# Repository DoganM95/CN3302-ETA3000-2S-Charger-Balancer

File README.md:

# Intro

A dual cell charger (3-6V 4A in, 8.4V ~3A out) combined with active balancing (1.3A).   
- The charging part makes sure to load the battery pack to 8.4v
- The balancing part makes sure to keep both batteries at the same voltage always, by charging the lower one using the higher one (active balancing)

Having these combined will in theory give the perfect 2S bms, so that batteries won't die, charge fast and don't waste energy.  

Any buyable bms i have tested so far fails to keep both batteries at the same voltage, so that one is e.g. 4.6v and the other 3.8v, resulting in 8.4v total but leading to damage/death of the overcharged cell, hence this proect to solve the issue and have a reliable, hackable solution.  

Still in concept phase, highly experimental and untested. Even the pcb traces are not wide enough to support the supplied current and would probably delaminate or catch fire.  

Releases starting with v1 or higher can be used and are tested.

# PCB

<table>
  <tr>
    <td>
      
    </td>
    <td>
      
    </td>
  </tr>
</table>

## BOM

Most parts a salvaged from commercially available modules, which are dirt-cheap on aliexpress:
- [Charging module (2S, 4A](https://a.aliexpress.com/_EuYAQFK)
- [Balancing module (2S, 1.3A, active)](https://s.click.aliexpress.com/e/_EuIdQJ6)

So all parts of those modules can be desoldered using a hot-plate and solder3d on this project's pcb.

<table>
  <thead>
    <tr>
      <th>Component Symbol</th>
      <th>Size</th>
      <th>Value</th>
      <th>Side Notes</th>
    </tr>
  </thead>
  <tbody>
    <tr><td>C1</td><td>0603</td><td>10nF</td><td></td></tr>
    <tr><td>C2</td><td>1206</td><td>22uF</td><td></td></tr>
    <tr><td>C3</td><td>0603</td><td>10nF</td><td></td></tr>
    <tr><td>C4</td><td>0603</td><td>10nF</td><td></td></tr>
    <tr><td>C5</td><td>0603</td><td>10nF</td><td></td></tr>
    <tr><td>C6</td><td>1206</td><td>22uF</td><td></td></tr>
    <tr><td>C7</td><td>1206</td><td>22uF</td><td></td></tr>
    <tr><td>C8</td><td>1206</td><td>22uF</td><td></td></tr>
    <tr><td>C9</td><td>1206</td><td>22uF</td><td></td></tr>
    <tr><td>C10</td><td>0603</td><td>10nF</td><td></td></tr>
    <tr><td>C11</td><td>1206</td><td>22uF</td><td></td></tr>
    <tr><td>C12</td><td>1206</td><td>22uF</td><td></td></tr>
    <tr><td>C13</td><td>1206</td><td>22uF</td><td></td></tr>
    <tr><td>C14</td><td>1206</td><td>22uF</td><td></td></tr>
    <tr><td>D1</td><td>sma</td><td>SS54 (Schottky)</td><td></td></tr>
    <tr><td>L1</td><td>0630 (6.6x6.6x3mm)</td><td>2.2 uH</td><td></td></tr>
    <tr><td>L2 / L3</td><td>any</td><td>2.2 uH</td><td>any that fits there by size</td></tr>
    <tr><td>LED1</td><td>0603</td><td>led</td><td>any color, check R3</td></tr>
    <tr><td>Q1</td><td>TO-252-2</td><td>KND3203b</td><td></td></tr>
    <tr><td>R1</td><td>0603</td><td>5.1 kOhm</td><td></td></tr>
    <tr><td>R2</td><td>0603</td><td>5.1 kOhm</td><td></td></tr>
    <tr><td>R3</td><td>0603</td><td>var Ohm</td><td>choose one that fits your LED1</td></tr>
    <tr><td>R4</td><td>0603</td><td>25 kOhm</td><td></td></tr>
    <tr><td>R5</td><td>2512</td><td>0.015 Ohm</td><td></td></tr>
    <tr><td>R6</td><td>0603</td><td>10 kOhm</td><td></td></tr>
    <tr><td>R7</td><td>0603</td><td>10 kOhm</td><td></td></tr>
    <tr><td>U1</td><td>sot23-6</td><td>ETA3000</td><td></td></tr>
    <tr><td>U2</td><td>smt</td><td>PC817X</td><td></td></tr>
    <tr><td>U3</td><td>sop8</td><td>CN3302</td><td></td></tr>
    <tr><td>U4</td><td>sot23-5</td><td>MIC5219 3.3v</td><td></td></tr>
  </tbody>
</table>

## Schematic

### By Datasheets

Follows the recommendations and schematics of the datasheets

### By reverse engineered chinese modules

Follows the reverse engineered chinese pcb modules, so they are merged into this pcb to minimize the need of additional components (just move parts over).

Todo

## Key Takeaways

- The status group of the `ETA3000` consisting of a red led and a 1k resistor use `BatC` as one pole and `SW` as the other. Thus it does not have a real `GND` but current flows with `BatC` acting as Vcc and `SW` acting as `GND` for the led
- The said red status led connections could also be exploited to power an optocoupler, so the `GND` stays independent for this part of the circuit and status becomes measurable using e.g. an arduino
- Connecting `BIAS` or `SW` of the `ETA3000` to the `GND`, which is the negative side of the 2 batteries connected in series, kills the IC and from there it gets very hot while being powered
- None of the 2 ic's (CN3302 && ETA3000) have a symbol in snapeda, so generic packages are used and pins renamed to match this ic

## Resources

### Charger IC: CN3302 (sop-8)

- [Datasheet (EN) of CN3302](https://github.com/DoganM95/2S-Charge-Balance-Pcb/files/13642784/CN3302.zh-CN.en.pdf)
- [Datasheet (CN) of CN3302](https://jlcpcb.com/partdetail/ShangHai_ConsonanceElec-CN3302/C559039)

### Active balancer IC: ETA3000 (sot23-6)
- [Writeup on ETA3000](https://www.beyondlogic.org/review-li-ion-lipo-lifepo4-lithium-battery-active-equalizer-balancer-energy-transfer-board/)
- [Datasheet of ETA3000](https://github.com/DoganM95/2S-Charge-Balance-Pcb/files/13648156/ETA3000-ETA.pdf)

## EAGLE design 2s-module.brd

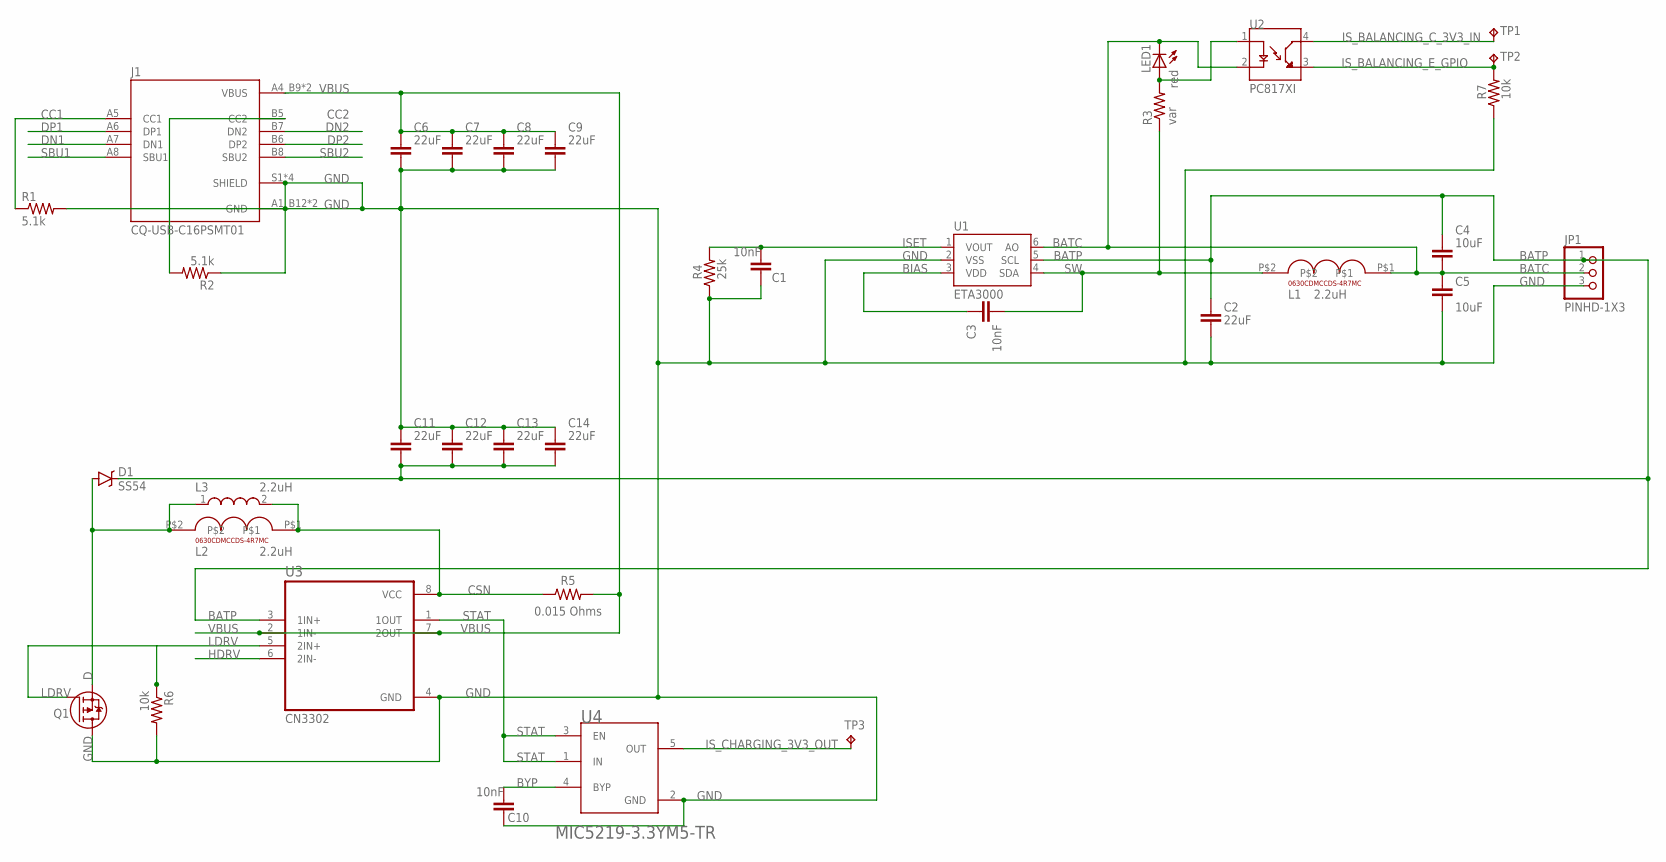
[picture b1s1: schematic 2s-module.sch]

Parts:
C1, C3, C10: 10nF; CAPC1608X85
C2, C6, C7, C8, C9, C11, C12, C13, C14: 22uF; CAPC3216X135
C4, C5: 10uF; CAPC1608X85
D1: SS54; DO-214AC
J1: CQ-USB-C16PSMT01; SHENZHEN-CHUANGQIN-TECHNOLOGY_CQ-USB-C16PSMT01
JP1: PINHD-1X3; 1X03
L1: 0630CDMCCDS-4R7MC
L2: 2.2uH; 0630CDMCCDS-4R7MC
L3: 2.2uH; INDM110100X380N
LED1: red; CHIPLED_0603
Q1: IRFR9020A; TO252
R1, R2: 5.1k; R0603
R3: var; R0603
R4: 25k; R0603
R5: 0.015 Ohms; RESC6332X71
R6, R7: 10k; R0603
TP1, TP2, TP3: TPB1,27; B1,27
U1: MCP4725; SOT23-6
U2: PC817XI; SOIC254P975X460-4N
U3: LM393DR; SOIC127P599X175-8N
U4: MICROCHIP_MIC5219-3_3YM5-TRMICROCHIP_MIC5219-3_3Y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; MICROCHIP_MIC5219-3_3YM5-TR_0

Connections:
BATC: C4.2, C5.1, JP1.2, L1.P$1, LED1.C, U1.6 (AO), U2.2 (C)
BATP: C2.1, C4.1, C11.2, C12.2, C13.2, C14.2, D1.C, JP1.1, U1.5 (SCL), U3.3 (1IN+)
BIAS: C3.2, U1.3 (VDD)
BYP: C10.2, U4.4 (BYP)
CC1: J1.A5 (CC1), R1.1
CC2: J1.B5 (CC2), R2.2
CSN: L2.P$1, L3.2, R5.1, U3.8 (VCC)
D: D1.A, L2.P$2, L3.1, Q1.2 (S)
DN1: J1.A7 (DN1)
DN2: J1.B7 (DN2)
DP1: J1.A6 (DP1)
DP2: J1.B6 (DP2)
GND: C1.1, C2.2, C5.2, C6.2, C7.2, C8.2, C9.2, C10.1, C11.1, C12.1, C13.1, C14.1, J1.A1_B12 (GND), J1.B1_A12 (GND), J1.S1 (SHIELD), J1.S2 (SHIELD), J1.S3 (SHIELD), J1.S4 (SHIELD), JP1.3, Q1.3 (D), R1.2, R2.1, R4.1, R6.2, R7.1, U1.2 (VSS), U3.4 (GND), U4.2 (GND)
HDRV: U3.6 (2IN-)
ISET: C1.2, R4.2, U1.1 (VOUT)
IS_BALANCING_C_3V3_IN: TP1.TP, U2.4 (CT)
IS_BALANCING_E_GPIO: R7.2, TP2.TP, U2.3 (ET)
IS_CHARGING_3V3_OUT: TP3.TP, U4.5 (OUT)
LDRV: Q1.1 (G), R6.1, U3.5 (2IN+)
unnamed: LED1.A, R3.2, U2.1 (A)
SBU1: J1.A8 (SBU1)
SBU2: J1.B8 (SBU2)
STAT: U3.1 (1OUT), U4.1 (IN), U4.3 (EN)
SW: C3.1, L1.P$2, R3.1, U1.4 (SDA)
VBUS: C6.1, C7.1, C8.1, C9.1, J1.A4_B9 (VBUS), J1.B4_A9 (VBUS), R5.2, U3.2 (1IN-), U3.7 (2OUT)

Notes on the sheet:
ETA3000
2.2uH
CN3302

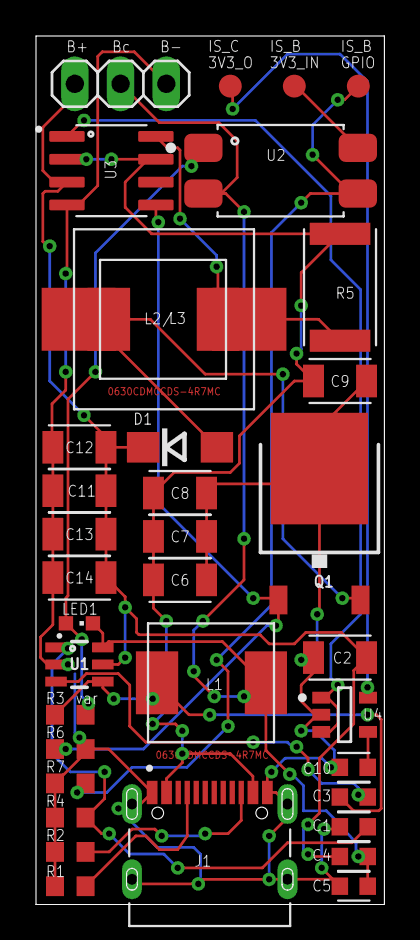
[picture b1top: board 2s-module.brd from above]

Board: 2 copper layers, 19.4 x 48.2 mm, 36 parts (0 on the bottom side), 18 nets.

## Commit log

2023-12-12 init schematic & board
2023-12-12 build balancer prototype
2023-12-12 add optocoupler
2023-12-13 finish initial prototype, inductors may change
2023-12-14 fix some parts in sch
2023-12-15 add fallback inductor
2023-12-15 build board to be wired
2023-12-15 add alternative direction indicators
2023-12-15 rearrange more to save space
2023-12-15 move buried component
2023-12-15 route airwires
2023-12-15 low amp version, to be overwritten with new design
2024-03-24 Create init
2024-03-24 Rename snippet.png to snippet.png
2024-03-24 Rename table.png to table.png
2024-04-11 [ImgBot] Optimize images
    *Total -- 145.71kb -> 86.52kb (40.62%)
    /assets/table.png -- 132.50kb -> 75.15kb (43.28%)
    /assets/snippet.png -- 13.22kb -> 11.37kb (13.94%)
2024-12-07 add initial release
2024-12-07 trim assets
2024-12-07 update BOM for assembly
2024-12-07 fix bom order
2024-12-09 turn bom into table

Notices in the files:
parts and their libraries:
SparkFun-IC-Conversion: Licensing: Creative Commons ShareAlike 4.0 International - https://creativecommons.org/licenses/by-sa/4.0
